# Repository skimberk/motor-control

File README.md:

# motor-control

Fixed `Could not determine GDB version using command` error in STM32CubeIDE by installing `sudo apt install libncurses5`.

At first I was getting an error `failed to start gdb server`. I unplugged and replugged the ST-Link while in STM32CubeIDE and was prompted to upgrade the firmware. I upgraded the firmware and it started working.

### Getting SWV Trace to work with ST-Link V2 chinese clone

Summary: I had to solder a piece of magnet wire to one of the pins on the chip of the ST-Link so that I could connect it to the `TRACESWO` pin on my STM32F103 Blue Pill. Here's the tutorial I (more or less) followed: https://lujji.github.io/blog/stlink-clone-trace/

After a lot of flailing (and thinking that maybe my version of STM32CubeIDE was just broken), I finally got SWV Trace working. It turns out that it requires having a pin on the ST-Link connected to the SWO pin on the STM32. For some reason, though, this pin isn't one of the pins that's normally accessible on the chinese ST-Link clones, so I had to solder on a piece of magnet wire. It works now!

1. Take apart the ST-Link. I found that if I held the metal case and pushed on the USB connector, the PCB (which is attached to the USB connector) popped out pretty easily.

2. Solder a length of magnet wire (just thin copper wire with enamel insulation) onto pin 31 (AKA `PA10`) of the chip inside the ST-Link. See tutorial for more info: https://lujji.github.io/blog/stlink-clone-trace/ The chip in my ST-Link is a CKS32F103C8T6, which appears to be a clone of the original STM32F103C8T6. It worked for me, though, so having a cloned chip wasn't a problem.

3. Solder a piece of 22 gauge solid copper wire onto the end of the magnet wire for breadboarding, then put the metal case back onto the ST-Link. I also superglued the magnet wire onto the PCB to (hopefully) prevent it from getting pulled off the trace and cut a little groove into the plastic pin holder thing (?) for the magnet wire to pass through when the case is back on.

4. Enable SWV in STM32CubeIDE. Open the `Debug Configuations...` under the Debug icon (the weird little insect/tick looking thing). In the `Debugger` tab, enable `Serial Wire Viewer (SWV)` and make sure the `Core Clock` is set to your system clock (which you can find in STM32CubeIDE under `SYSCLK`). 

5. In the Debugger perspective, click on `Window -> Show View -> SWV -> SWV Data Trace` (and `SWV Data Trace Timeline Graph`) to be able to view the SWV output.

6. Enable the `SYS_JTDO-TRACESWO` pin on your microcontroller (on my STM32F103C8 this was on pin `PB3`) and set the `Debug` method under `SYS` (which is itself under `System Core` in STM32CubeMX) to `Trace Asynchronous Sw`.

7. Run the generated code (in debug mode, by pressing the little bug icon) on your microcontroller. Make sure the `TRACESWO` on your microntroller (`PB3` in my case) is connected to the new pin you soldered onto your ST-Link. While the debugger is paused on the first breakpoint (I wasn't able to get this working otherwise) bring up the SWV settings by clicking on the wrench icon under the `SWV Data Trace` tab. Under `ITM Stimulus Ports`, enable pin 0. Start tracing by clicking the red circle.

Some of these steps might not be necessary, but it's what I ended up doing to get SWV working. I also redirected `printf` output to the `SWV Data Trace` console by adding the following code to my `main.c`:

```
// Just make sure stdio.h is included
#include "stdio.h"

// ... some other code in between

int _write(int32_t file, uint8_t *ptr, int32_t len) {
	/* Implement your write code here, this is used by puts and printf for example */
	int i = 0;
	for(i=0; i < len; i++) {
		ITM_SendChar((*ptr++));
	}
	return len;
}
```

### Getting I2C working (just use pullup resistors)

I was having difficulties getting I2C to work on my STM32 (using STM32CubeIDE and STM32CubeMX). `HAL_I2C_Master_Transmit` would always either return `HAL_BUSY` or `HAL_ERROR`. When I connected my oscilloscope to `SCL` it would always return `HAL_BUSY`, whereas when it wasn't connected to anything it would return `HAL_ERROR`. This, along with the fact that the pin appeared to always be low on the oscilloscope, was a little suspicious. I added some 2.2K pullup resistors to both `SCL` and `SDA` and now it's working fine!

### Magical bug?

I've been working to add an encoder to my cheap brushless motor by gluing a magnet to the back of the shaft and placing a magnetic encoder (an AS5600 supported by popsicle sticks) above it. I had the AS5600 hooked up to the oscilloscope, and noticed that at certain angles of the motor, there was some (big!) noise. However, it seemed to only appear when I was touching the motor. The noise (well, maybe not noise after all) was exactly 60Hz.

After a bit more experimentation, I realized that my foot was on an extension cord cable, and when I moved my foot away, the noise disappeared. If I put my foot back on the cable, the noise reappeared. Weird, but I don't know enough about electronics to really be able to debug it, so I decided to fix the issue by just not putting my foot on the extension cable any more.

I made some modification to the encoder so it would no longer be on a breadboard and so it would instead be glued to the back of the motor (a more permanent and easier to work with arrangement). To my dismay, the "noise" was back, and it was there independent of the position of my foot. Heck, it was even there when I wasn't touching the motor! It was at this point that I realized that the "noise" disappeared when the encoder indicated 180 degrees and I remembered that the AS5600 has a pin (called DIR) which sets whether the angle increased on clockwise or counterclockwise rotation. I had been lazy and hadn't attached the pin to anything, figuring it would have some default. The "noise" looked suspiciously as if this setting were being switched back and forth at 60Hz. Hmm, maybe I should have attached the pin to something after all. To test whether I was onto something, I quickly connected the DIR pin to 3.3V (the logic voltage) and, lo and behold, the "noise" disappeared!

I really have no idea how the mains voltage was causing the DIR setting to switch, especially when it only happened when my foot was on the extension cable. But I have a feeling it has something to do with the sensitivity of a floating MOSFET, and with charges getting induced by the alternating current in the cable.

### STM32CubeIDE install location (on Ubuntu)

I was having a hard time figuring out where STM32CubeIDE was installed so that I could run it as `sudo` and update it. I found it in `/opt/st/`.

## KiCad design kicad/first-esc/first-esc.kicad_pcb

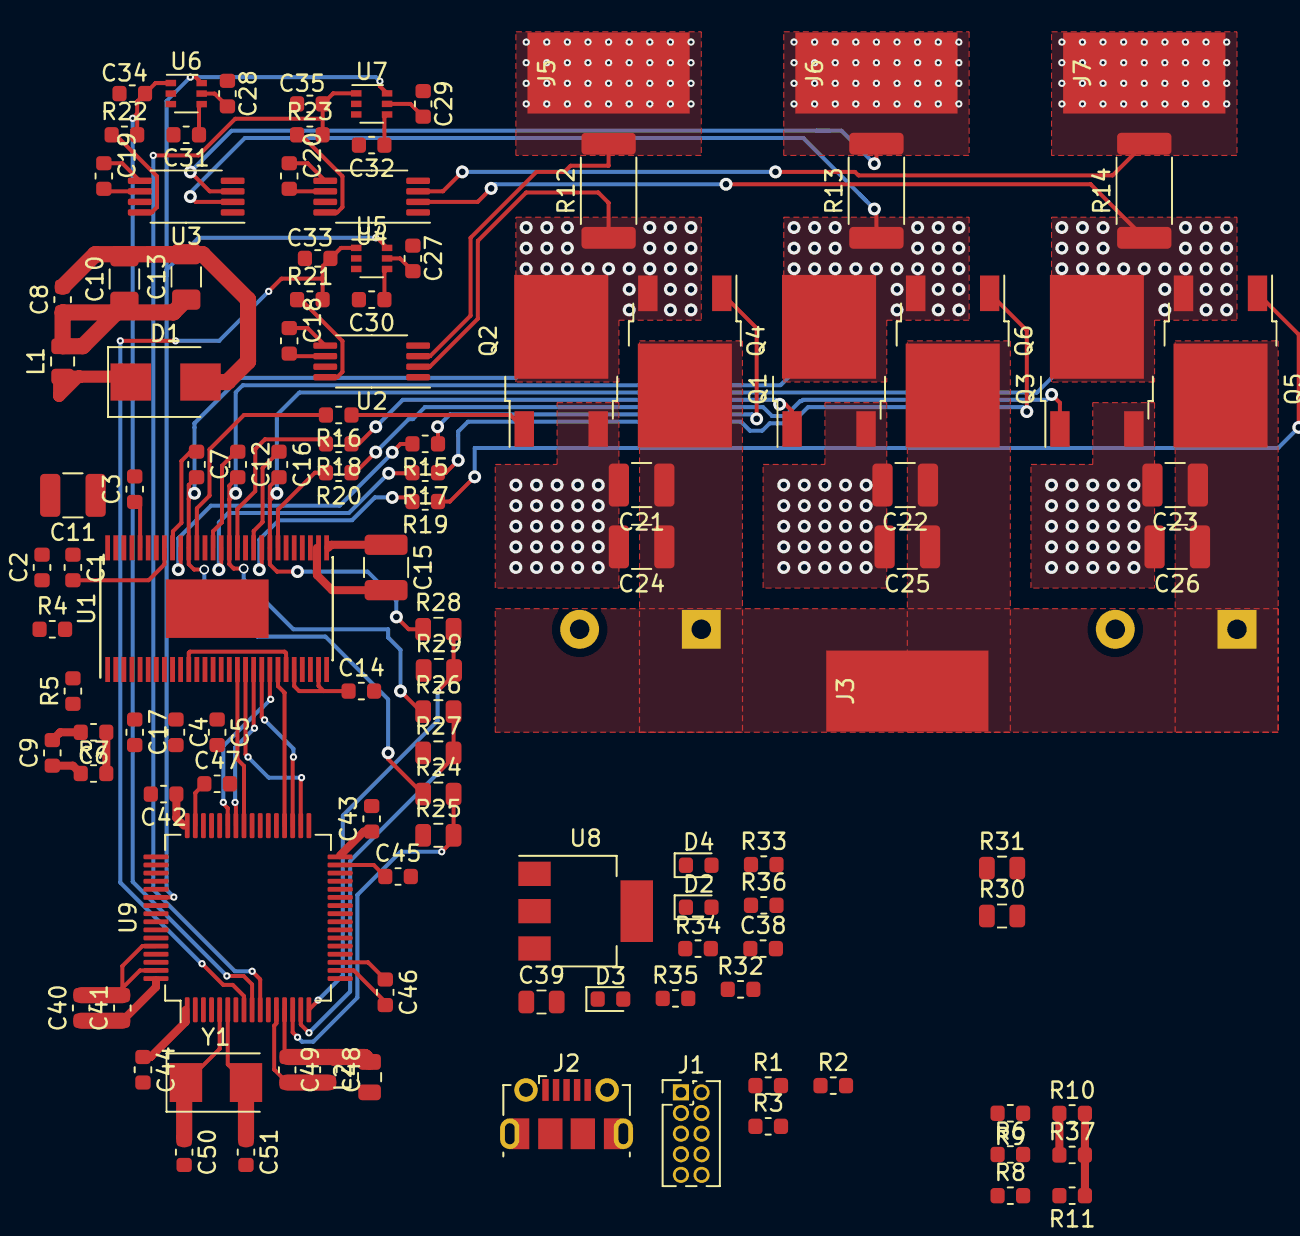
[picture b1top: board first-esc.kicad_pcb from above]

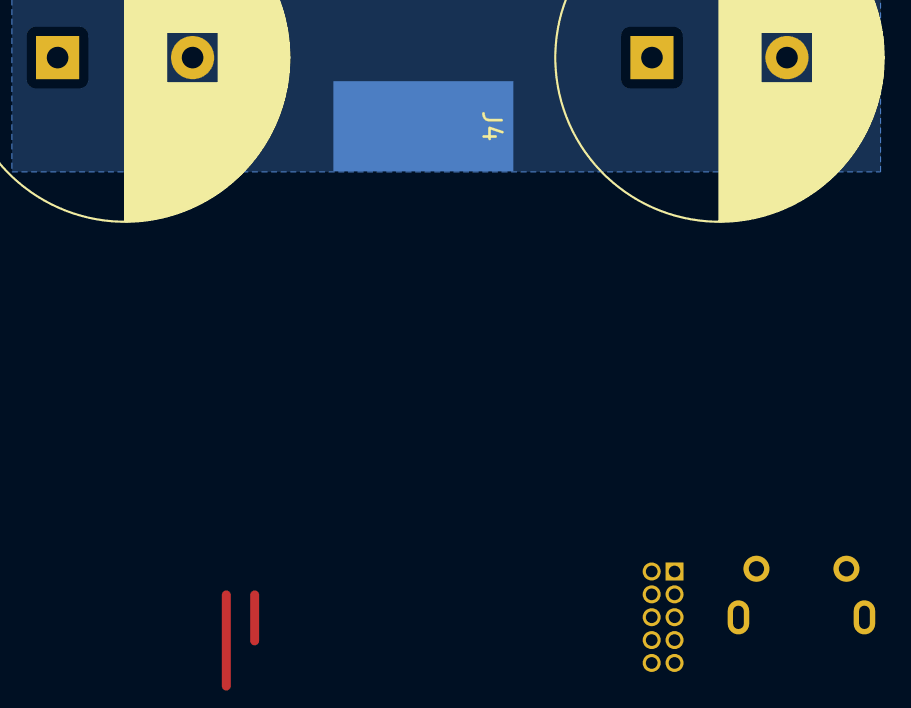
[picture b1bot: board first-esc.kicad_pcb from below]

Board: 2 copper layers, 117 parts (3 on the bottom side), 84 nets.

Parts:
C1, C3, C7, C12, C16, C41, C42, C43, C44, C46: 100n; C_0603_1608Metric
C2, C30, C31, C32: 15n; C_0603_1608Metric
C4, C14, C18, C19, C20, C27, C28, C29, C38, C45, C47: 2u2; C_0603_1608Metric
C5: 22n; C_0603_1608Metric
C6: 0; C_0603_1608Metric
C8, C40: 4u7; C_0603_1608Metric
C9: 2n2; C_0603_1608Metric
C10, C13: 47u; C_1206_3216Metric
C11, C15, C21, C22, C23, C24, C25, C26: 4u7; C_1210_3225Metric
C17, C48: 1u; C_0603_1608Metric
C33, C34, C35: 1n; C_0603_1608Metric
C36, C37: 680u; CP_Radial_D18.0mm_P7.50mm
C39: 22u; C_0805_2012Metric
C49: 10n; C_0603_1608Metric
C50, C51: 30p; C_0603_1608Metric
D1: Schottky_100v; D_SMB
D2: RED; LED_0603_1608Metric
D3: GREEN; LED_0603_1608Metric
D4: BLUE; LED_0603_1608Metric
J1: Conn_ARM_JTAG_SWD_10; PinHeader_2x05_P1.27mm_Vertical
J2: USB_OTG; USB_Micro-B_Molex-105017-0001
J3: Supply; SolderWirePad_1x01_SMD_5x10mm
J4: Gnd; SolderWirePad_1x01_SMD_5x10mm
J5: PH_A; SolderWirePad_1x01_SMD_5x10mm
J6: PH_B; SolderWirePad_1x01_SMD_5x10mm
J7: PH_C; SolderWirePad_1x01_SMD_5x10mm
L1: 22u; L_0805_2012Metric
L2: 47n; L_0805_2012Metric
Q1, Q2, Q3, Q4, Q5, Q6: Q_NMOS_GDS; TO-252-2
R1, R9: 0R; R_0603_1608Metric
R2, R3: 22R; R_0603_1608Metric
R4, R6, R8, R11, R33: 10k; R_0603_1608Metric
R5: 220k; R_0603_1608Metric
R7: 100k; R_0603_1608Metric
R10: 30k; R_0603_1608Metric
R12, R13, R14: 0.002R; R_2512_6332Metric
R15, R16, R17, R18, R19, R20: 4R7; R_0603_1608Metric
R21, R22, R23: 1k; R_0603_1608Metric
R24, R26, R28, R30: 39k; R_0805_2012Metric
R25, R27, R29, R31: 2k2; R_0805_2012Metric
R32: NTC 10k; R_0603_1608Metric
R34, R35, R36: 220R; R_0603_1608Metric
R37: 1k5; R_0603_1608Metric
U1: DRV8302DCAR; HTSSOP-56-1EP_6.1x14mm_P0.5mm_EP3.61x6.35mm
U2, U3, U4: INA240A2PW; TSSOP-8_4.4x3mm_P0.65mm
U5, U6, U7: BL1551; SOT-363_SC-70-6
U8: AMS1117-3.3; SOT-223-3_TabPin2
U9: STM32F405RGTx; LQFP-64_10x10mm_P0.5mm
Y1: 8M; Crystal_SMD_5032-2Pin_5.0x3.2mm

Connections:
+3.3VA: C48.1, C49.1, L2.2, U2.7, U3.7, U4.7, U9.13
+3V3: C8.1, C10.1, C13.1, C18.1, C19.1, C20.1, C27.1, C28.1, C29.1, C39.1, C40.1, C41.1, C42.1, C43.1, C44.1, C46.1, D4.2, J1.1, L1.2, L2.1, R4.1, R6.2, R8.2, R10.1, R32.2, R37.1, U1.9, U2.5, U3.5, U4.5, U5.5, U6.5, U7.5, U8.2, U9.1, U9.19, U9.32, U9.48, U9.64
+5V: R1.2, U8.3
/CURR_A: C33.1, R21.2, U5.1, U9.8
/CURR_B: C34.1, R22.2, U6.1, U9.9
/CURR_C: C35.1, R23.2, U7.1, U9.10
/GateDriver/COMP: C6.1, R7.2, U1.2
/GateDriver/DTC: R9.2, U1.7
/GateDriver/DVDD: C17.1, U1.11, U1.23
/GateDriver/EN_GATE: U1.16, U9.57
/GateDriver/GH_A: R15.2, U1.47
/GateDriver/GH_B: R17.2, U1.42
/GateDriver/GH_C: R19.2, U1.37
/GateDriver/GL_A: R16.2, U1.45
/GateDriver/GL_B: R18.2, U1.40
/GateDriver/GL_C: R20.2, U1.35
/GateDriver/INL_A: U1.18, U9.34
/GateDriver/INL_B: U1.20, U9.35
/GateDriver/INL_C: U1.22, U9.36
/GateDriver/PH: C3.2, D1.1, L1.1, U1.50, U1.51
/GateDriver/REF: C14.1, U1.24, U1.27
/GateDriver/SH_A: C7.2, Q1.3, Q2.2, R12.1, R24.1, U1.46, U2.2
/GateDriver/SH_B: C12.2, Q3.3, Q4.2, R13.1, R26.1, U1.41, U3.2
/GateDriver/SH_C: C16.2, Q5.3, Q6.2, R14.1, R28.1, U1.36, U4.2
/GateDriver/SUPPLY: C11.1, C15.1, C21.1, C22.1, C23.1, C24.1, C25.1, C26.1, C36.1, C37.1, J3.1, Q1.2, Q3.2, Q5.2, R30.1, U1.29, U1.53, U1.54
/GateDriver/VSENSE: R10.2, R11.1, R37.2, U1.3
/MCU/HSE_IN: C50.1, U9.5, Y1.1
/MCU/HSE_OUT: C51.1, U9.6, Y1.2
/MCU/H_A: U1.17, U9.41
/MCU/H_B: U1.19, U9.42
/MCU/H_C: U1.21, U9.43
/MCU/JTDI: J1.8, U9.50
/MCU/LED_GREEN: D3.2, U9.26
/MCU/LED_RED: D2.2, U9.27
/MCU/NRST: J1.10, U9.7
/MCU/SWCLK: J1.4, U9.49
/MCU/SWDIO: J1.2, U9.46
/MCU/SWO: J1.6, U9.55
/MCU/USB_D+: R2.1, U9.45
/MCU/USB_D-: R3.1, U9.44
/Power/CURR_A_RAW: R21.1, U2.8
/Power/CURR_B_RAW: R22.1, U3.8
/Power/CURR_C_RAW: R23.1, U4.8
/Power/CURR_FILTER: U5.6, U6.6, U7.6, U9.54
/Power/PH_A: J5.1, R12.2, U2.3
/Power/PH_B: J6.1, R13.2, U3.3
/Power/PH_C: J7.1, R14.2, U4.3
/TEMP: C38.1, R32.1, R33.2, U9.17
/VOLT_A: R24.2, R25.2, U9.14
/VOLT_B: R26.2, R27.2, U9.15
/VOLT_C: R28.2, R29.2, U9.16
/VOLT_SUPPLY: R30.2, R31.2, U9.11
GND: C1.1, C2.1, C4.2, C6.2, C8.2, C9.2, C10.2, C11.2, C13.2, C14.2, C15.2, C17.2, C18.2, C19.2, C20.2, C21.2, C22.2, C23.2, C24.2, C25.2, C26.2, C27.2, C28.2, C29.2, C30.2, C31.2, C32.2, C33.2, C34.2, C35.2, C36.2, C37.2, C38.2, C39.2, C40.2, C41.2, C42.2, C43.2, C44.2, C45.2, C46.2, C47.2, C48.2, C49.2, C50.2, C51.2, D1.2, J1.3, J1.5, J2.5, J2.6, J4.1, Q2.3, Q4.3, Q6.3, R5.1, R9.1, R11.2, R25.1, R27.1, R29.1, R31.1, R33.1, R34.1, R35.1, R36.1, U1.8, U1.10, U1.12, U1.28, U1.30, U1.31, U1.32, U1.33, U1.34, U1.39, U1.44, U1.57, U2.1, U2.4, U2.6, U3.1, U3.4, U3.6, U4.1, U4.4, U4.6, U5.2, U6.2, U7.2, U8.1, U9.12, U9.18, U9.60, U9.63
unnamed: C1.2, U1.49
unnamed: C2.2, U1.56
unnamed: C3.1, U1.52
unnamed: C4.1, U1.13
unnamed: C5.1, U1.14
unnamed: C5.2, U1.15
unnamed: C7.1, U1.48
unnamed: C9.1, R7.1
unnamed: C12.1, U1.43
unnamed: C16.1, U1.38
unnamed: C30.1, U5.4
unnamed: C31.1, U6.4
unnamed: C32.1, U7.4
unnamed: C45.1, U9.31
unnamed: C47.1, U9.47
unnamed: D2.1, R34.2
unnamed: D3.1, R35.2
unnamed: D4.1, R36.2
unnamed: J2.1, R1.1
unnamed: J2.2, R3.2
unnamed: J2.3, R2.2
unnamed: Q1.1, R15.1
unnamed: Q2.1, R16.1
unnamed: Q3.1, R17.1
unnamed: Q4.1, R18.1
unnamed: Q5.1, R19.1
unnamed: Q6.1, R20.1
unnamed: R4.2, U1.4
unnamed: R5.2, U1.1
unnamed: R6.1, U1.6
unnamed: R8.1, U1.5

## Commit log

2020-08-23 experimenting
2020-08-23 trying to figure out combine PWM
2020-08-23 minimum working combine example
2020-08-23 used constants in combine example
2020-08-23 combine phase shift
2020-08-29 learning julia and simulating pendulum and pendulum on cart
2020-09-09 inverted pendulum and combine pwm with more outputs
2020-09-13 fixed combine
2020-09-15 began working on svpwm
2020-09-16 svpwm improvements
2020-09-16 started experimenting with stm32
2020-09-16 got stm32 pwm (complementary) working
2020-09-18 make sure largest value is 1
2020-09-18 simplified svpwm implementation
2020-09-18 renamed blink01 to svpwm
2020-09-18 (hopefully) working stm32 svpwm
2020-09-18 lil comment
2020-09-18 svpwm actually works (i think)
2020-09-25 added bldc simulation
2020-09-25 removed bemfb (for now)
2020-09-25 started work on observer, and changed controller frequency
2020-09-26 OOPS had to fixed svpwm, two variables were swapped which resulted in incorrect values in second sector
2020-09-26 fixed SVPWM in stm32 code (plus a bunch of other debugging and experimentation
2020-09-28 further fiddling
2020-09-28 copied to make observer.py
2020-09-28 removed cruft
2020-09-28 remove negative voltages
2020-09-28 started writing observer
2020-09-30 a bunch of simulink experimentation, got PMSM and SPWM kinda working
2020-09-30 got observer working maybe i hope
2020-09-30 it actually looks like it works
2020-09-30 holy crap, i think it works
2020-10-04 added svpwm
2020-10-10 organizing
2020-10-11 added comments to inverted pendulum math
2020-10-11 clarified comment
2020-10-11 copied inverted pendulum for pendulum on wheel
2020-10-11 began making wheel changes
2020-10-12 got basic balance simulation working
2020-10-12 balancing is working
2020-10-12 added to gitignore
2020-10-12 removed gitignored files/added some ignored modifications
2020-10-12 working on jacobians/linearization
2020-10-12 LQR control is working!!! did some matlab calculation to find gains, switched rod theta so upright is 0 (not pi), and simulated!!
2020-10-12 removed unused comments
2020-10-12 drive around with arrow keys!
2020-10-17 added small arrow key acceleration
2020-10-17 made pin A11 an analog input
2020-10-17 jk, I don't think that actually enabled analog input, hopefully this does
2020-10-18 actually got adc working and (kindof) driving the motor with the magnetic encoder
2020-10-18 added i2c?
2020-10-19 got swv trace debugging working
2020-10-19 added instructions for how I got SWV debugging working
2020-10-19 fixed typo and added another link to the swv trace tutorial
2020-10-19 typo and info about supergluing magnet wire
2020-10-20 got i2c workinggit add -A!
2020-10-20 reading angle, trying to get motor working again
2020-10-21 rudimentary speed control with the magnetic encoder is working!!!!
2020-10-21 increased clock and i2c speeds, and got (rudimentary) position control working
2020-10-21 disabled ADC (and updated STM32CubeIDE)
2020-10-21 added stm32cubeide location
2020-10-23 Added different modes
2020-10-24 hopefully multi-channel ADC with DMA (fingers crossed)
2020-10-24 and adc is working, just had to increase sample time so that swv debug still works
2020-10-24 started working on sensorless, current sensing doesn't seem very accurate
2020-11-08 started designing PCB
2020-11-09 (hopefully) finishing up PCB schematic
2020-11-10 mostly finished schematic, started PCB layout
2020-11-11 mostly finished up DRV and MCU pcb layout
2020-11-11 checkpoint before redoing mcu and drv
2020-11-11 removed traces
2020-11-11 kinda coming together?
